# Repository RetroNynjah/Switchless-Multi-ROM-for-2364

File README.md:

# Retroninja Switchless Multi-ROM for 2364 ROMs

<br/>

A switchless multi-ROM for 2364 ROM (24-pin) type applications. The switch is controlled by an MCU that is picking up predefined magic words on the data bus.  
This is a more generic and further developed version of my previous 1541 Multi-ROM design.

Example use cases:
* ROM switch for the Commodore 1541 disk drive controlled by DOS commands.
* Menu driven Kernal switch for Commodore C64 (longboards)
* Menu driven Kernal switch for Commodore VIC-20
* You tell me

Check the Applications folder for examples on how to use it for the use cases above.

Check the Technical Guide for a general technical description, build instructions and BOM.

  <br/>

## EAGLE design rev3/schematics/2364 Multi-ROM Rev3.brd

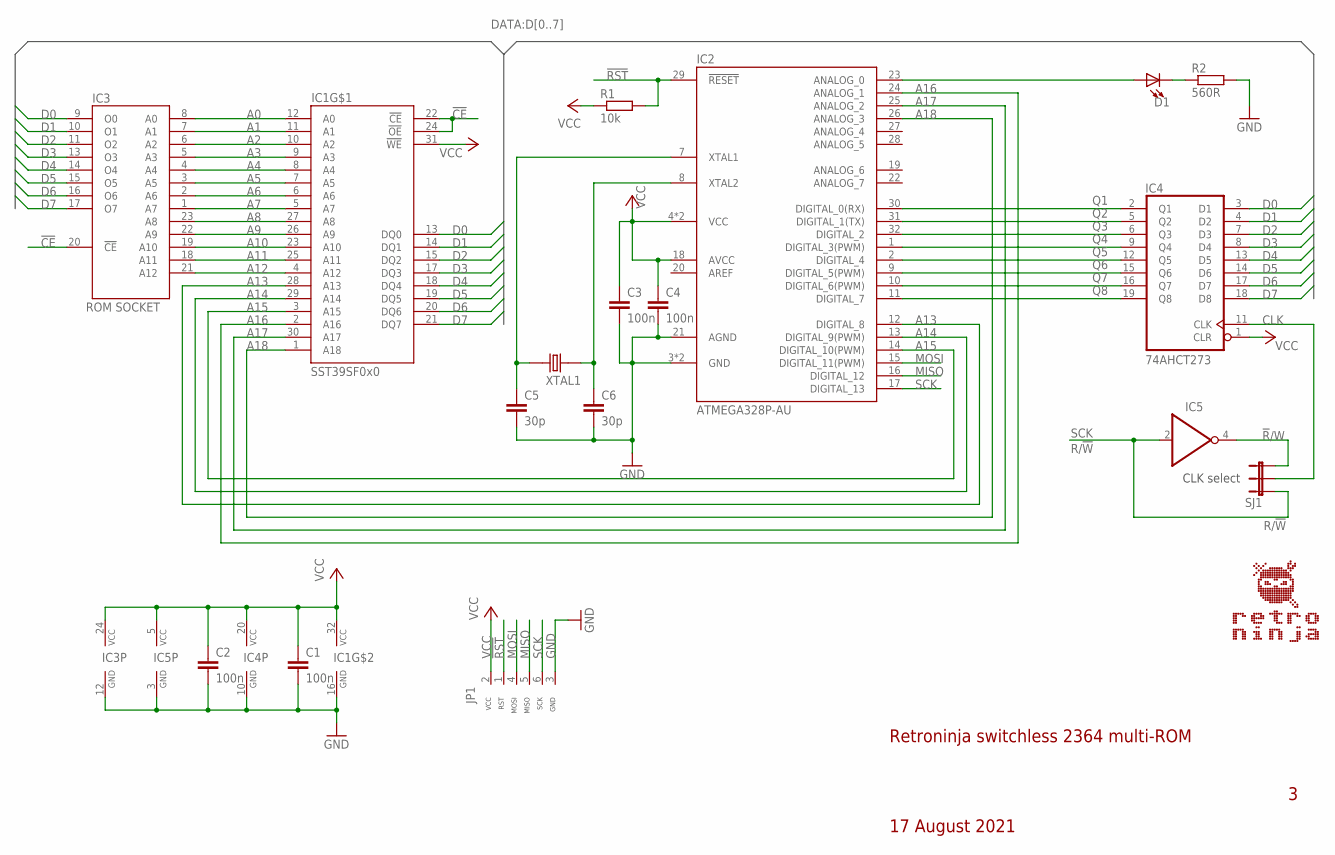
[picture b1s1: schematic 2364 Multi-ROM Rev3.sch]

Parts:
C1, C2, C3, C4: 100n; C0805
C5, C6: 30p; C0805
D1: LED_0805; LED0805
IC1: SST39SF0x0; PLCC32_SHORT
IC2: ATMEGA328P-AU; TQFP32
IC3: ROM SOCKET; DIL24-6_DOWNPINS
IC4: 74AHCT273; SO20
IC5: 741G04_SOT23; SOT23-5
JP1: ICSP_CONNECTOR_TL866_RIGHT2; HEADER_1X6_RIGHT
R1: 10k; R0805
R2: 560R; R0805
SJ1: JUMPER-3SJ; SJ-3
XTAL1: CRYSTAL; CRYSTAL_SMD-2_7X4X2.3

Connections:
!CE: IC1.22 (!CE), IC1.24 (!OE), IC3.20 (!CE)
!R!/W: IC5.4 (O), SJ1.3
!RST: IC2.29 (!RESET), JP1.1 (RST), R1.2
A0: IC1.12 (A0), IC3.8 (A0)
A1: IC1.11 (A1), IC3.7 (A1)
A2: IC1.10 (A2), IC3.6 (A2)
A3: IC1.9 (A3), IC3.5 (A3)
A4: IC1.8 (A4), IC3.4 (A4)
A5: IC1.7 (A5), IC3.3 (A5)
A6: IC1.6 (A6), IC3.2 (A6)
A7: IC1.5 (A7), IC3.1 (A7)
A8: IC1.27 (A8), IC3.23 (A8)
A9: IC1.26 (A9), IC3.22 (A9)
A10: IC1.23 (A10), IC3.19 (A10)
A11: IC1.25 (A11), IC3.18 (A11)
A12: IC1.4 (A12), IC3.21 (A12)
A13: IC1.28 (A13), IC2.12 (DIGITAL_8)
A14: IC1.29 (A14), IC2.13 (DIGITAL_9(PWM))
A15: IC1.3 (A15), IC2.14 (DIGITAL_10(PWM))
A16: IC1.2 (A16), IC2.24 (ANALOG_1)
A17: IC1.30 (A17), IC2.25 (ANALOG_2)
A18: IC1.1 (A18), IC2.26 (ANALOG_3)
CLK: IC4.11 (CLK), SJ1.2
D0: IC1.13 (DQ0), IC3.9 (O0), IC4.3 (D1)
D1: IC1.14 (DQ1), IC3.10 (O1), IC4.4 (D2)
D2: IC1.15 (DQ2), IC3.11 (O2), IC4.7 (D3)
D3: IC1.17 (DQ3), IC3.13 (O3), IC4.8 (D4)
D4: IC1.18 (DQ4), IC3.14 (O4), IC4.13 (D5)
D5: IC1.19 (DQ5), IC3.15 (O5), IC4.14 (D6)
D6: IC1.20 (DQ6), IC3.16 (O6), IC4.17 (D7)
D7: IC1.21 (DQ7), IC3.17 (O7), IC4.18 (D8)
GND: C1.2, C2.2, C3.2, C4.2, C5.2, C6.2, IC1.16 (GND), IC2.3 (GND), IC2.5 (GND), IC2.21 (AGND), IC3.12 (GND), IC4.10 (GND), IC5.3 (GND), JP1.3 (GND), R2.2
MISO: IC2.16 (DIGITAL_12), JP1.5 (MISO)
MOSI: IC2.15 (DIGITAL_11(PWM)), JP1.4 (MOSI)
unnamed: C6.1, IC2.8 (XTAL2), XTAL1.1
unnamed: C5.1, IC2.7 (XTAL1), XTAL1.2
unnamed: D1.A, IC2.23 (ANALOG_0)
unnamed: D1.C, R2.1
Q1: IC2.30 (DIGITAL_0(RX)), IC4.2 (Q1)
Q2: IC2.31 (DIGITAL_1(TX)), IC4.5 (Q2)
Q3: IC2.32 (DIGITAL_2), IC4.6 (Q3)
Q4: IC2.1 (DIGITAL_3(PWM)), IC4.9 (Q4)
Q5: IC2.2 (DIGITAL_4), IC4.12 (Q5)
Q6: IC2.9 (DIGITAL_5(PWM)), IC4.15 (Q6)
Q7: IC2.10 (DIGITAL_6(PWM)), IC4.16 (Q7)
Q8: IC2.11 (DIGITAL_7), IC4.19 (Q8)
SCK: IC2.17 (DIGITAL_13), IC5.2 (I), JP1.6 (SCK), SJ1.1
VCC: C1.1, C2.1, C3.1, C4.1, IC1.31 (!WE), IC1.32 (VCC), IC2.4 (VCC), IC2.6 (VCC), IC2.18 (AVCC), IC3.24 (VCC), IC4.1 (CLR), IC4.20 (VCC), IC5.5 (VCC), JP1.2 (VCC), R1.1

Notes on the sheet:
R/!W
Retroninja switchless 2364 multi-ROM
17 August 2021
CLK select

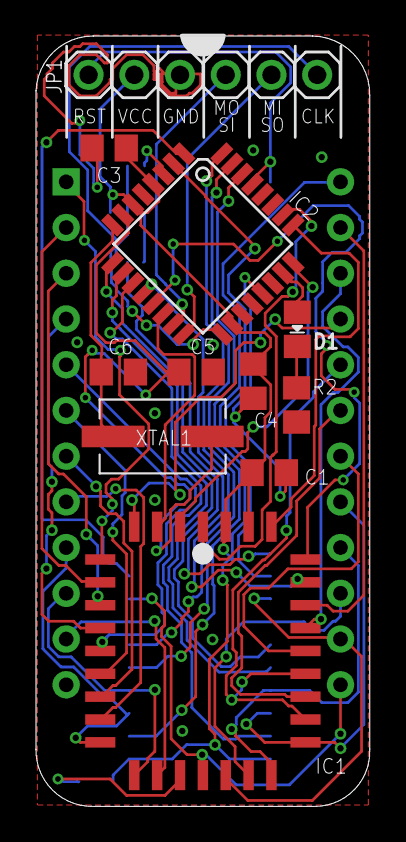
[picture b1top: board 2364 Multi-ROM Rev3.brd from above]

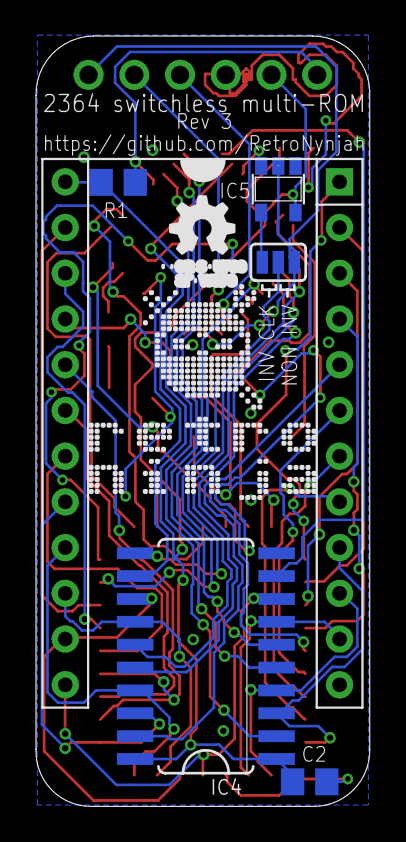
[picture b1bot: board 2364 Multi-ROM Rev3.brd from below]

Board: 2 copper layers, 18.5 x 42.8 mm, 19 parts (7 on the bottom side), 48 nets.

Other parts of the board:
U$1: RETRONINJA_12MM
U$2: OSHW_5MM

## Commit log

2022-06-27 Initial upload
2022-07-07 CBM 1541 Firmware v1.1
    New firmware that matches PCB rev3.
2022-08-20 Updated techincal guide and multi-kernal user's guide
    Corrections in documention
2022-09-06 Mini-kernal updated to v1.4
    C64 mini-kernal updated to v1.4. C128DCR compatibility. Nothing new for C64 machines except for the version number.
2022-09-06 Updated Kernal Switch pictures and corrected user guide version
2022-09-07 Updated Kernal switch user guide
    Kernal switch user guide version 1.2 with Kernal ROM chip location and socket information
2022-10-04 BOM corrected in technical guide
2022-11-30 Mini-kernal version 1.5
    Minor change in keyboard detection to try and mitigate key bounce
2022-12-01 Recompiled 64 multi-kernal firmware
    Recompiled firmware using DIY AVR core
2023-01-03 Firmware v1.4 for C64 Kernal switch
    Version numbers aligned between firmware for different Kernal switches as functionality is the pretty much same for all switches.
    Improved handling of restore key functionality while in menu. This was originally done for the C128 Kernal switch but was ported to the C64 firmware to keep them as similar as possible.
    Code cleanup and some optimizations of main loop.
    Thanks Pär Högberg!
2023-01-09 Moved 1541 ROM switch firmware files
2023-01-10 New firmware version 1.2
    Incorporated reworked and optimized code and a number of fixes from the ROM-switch for 28-pin ROMs.
    Thanks to Pär Högberg for contributing code optimizations.
2023-04-15 Added VIC-20 Kernal switch
2023-08-27 Update vic20kernalmenu.bin
    Minor correction in menu settings of mini-kernal sample
2023-08-28 VIC-20 mini-kernal sample updated
    Updated kernal menu settings. No code changes-
2024-10-01 VIC-20 PCB 251037
    Added pictures of PCB 251037
2024-12-22 Updated C64 multi-ROM user guide
    Added connections for unnamed PAL Rev A motherboard known as 251022 or KU-14194HB
